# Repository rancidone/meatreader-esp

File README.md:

# Meatreader ESP32

ESP32-based wireless meat thermometer. Firmware reads up to 4 thermistor channels via ADS1115 ADC, applies Steinhart-Hart calibration, and exposes an HTTP API consumed by a web UI served from the device.

## Product Direction

This is a personal project in development, not a validated commercial thermometer. V0 demonstrated probe-to-phone readings. The later V2 board is assembled and has needed wiring repairs; the repository does not establish post-repair four-probe accuracy, Wi-Fi stability, or battery runtime. Implemented software features should not be read as hardware qualification results. The on-device display remains unfinished in MeatReader.

The [build story](https://mattmadeitwork.com/projects/meatreader/) documents the revisions and repairs.

**Web UI** (`thermometer-ui/`) is the primary interface — live dashboard, cook profiles, alerts, calibration, config, diagnostics, and firmware updates. Accessible from any browser on the local network, including mobile browsers.

**On-device TFT UI** (planned) will provide a heads-up status display with physical button navigation — no phone required during a cook.

The ESP32 firmware HTTP API is the integration surface. LAN-first; no cloud dependency.

## Repository Layout

```
firmware/          — ESP-IDF v5.5.3 C firmware (ESP32)
thermometer-ui/    — Svelte 5 + TypeScript web UI (served from device SPIFFS)
pcb/               — later board design and printable enclosure files
```

## HTTP API

All endpoints return JSON. The device runs an HTTP server on port 80.

| Method | Path | Description |
|--------|------|-------------|
| `GET` | `/dashboard` | **Consolidated** — snapshot + status + alerts in one call. `snapshot` is `null` until first sensor reading; never returns 503. Preferred for mobile clients. |
| `GET` | `/temps/latest` | Latest sensor snapshot (all channels). |
| `GET` | `/status` | Device health, uptime, firmware version, WiFi RSSI. |
| `GET` | `/device` | Static device metadata (platform, channel count, firmware). |
| `GET` | `/config` | Full config object: persisted / active / staged. |
| `PATCH` | `/config/staged` | Partial patch to staged config. |
| `POST` | `/config/apply` | Promote staged → active. |
| `POST` | `/config/commit` | Persist active → NVS. |
| `POST` | `/config/revert-staged` | Revert staged ← active. |
| `POST` | `/config/revert-active` | Revert active ← persisted (NVS). |
| `GET` | `/alerts` | Per-channel alert config + live `triggered` state. |
| `PATCH` | `/alerts/staged` | Update staged alert config. |
| `GET` | `/profiles` | All 8 cook profile slots (empty slots have `name=""`). |
| `PUT` | `/profiles/{id}` | Write a cook profile slot. |
| `DELETE` | `/profiles/{id}` | Clear a cook profile slot. |
| `GET` | `/calibration/live` | Live calibration reading for a channel (`?ch=N`). |
| `POST` | `/calibration/session/start` | Begin calibration session. |
| `POST` | `/calibration/point/capture` | Capture a calibration point. |
| `POST` | `/calibration/solve` | Solve Steinhart-Hart coefficients from captured points. |
| `POST` | `/calibration/accept` | Write solved coefficients to staged config. |
| `GET` | `/metrics` | Prometheus text metrics (temperature, resistance, ADC, RSSI, uptime). |
| `GET` | `/events` | Server-Sent Events stream — emits snapshot JSON on each sensor tick. |
| `POST` | `/ota` | Upload firmware binary for OTA update. |
| `POST` | `/ota/rollback` | Roll back to the previous OTA partition. |

TypeScript API types are in `thermometer-ui/src/lib/api/types.ts`. The browser client is in `thermometer-ui/src/lib/api/client.ts`, with the live SSE transport in `thermometer-ui/src/lib/api/live.ts`. There is no separate native mobile application in this repository.

The [archived hardware repository](https://github.com/rancidone/meatreader-pcb) preserves earlier hardware work. Check the physical board revision against `pcb/` and the constants in `firmware/components/board/` before building or flashing.

## Production Build & Flash

Flash the full self-contained firmware (ESP32 + web UI served from SPIFFS):

### Prerequisites

1. Install [ESP-IDF v5.5.3](https://docs.espressif.com/projects/esp-idf/en/v5.5.3/esp32/get-started/)
2. Install Node.js 22.12+ (or a compatible newer LTS release).

### One-command flash

```bash
source $IDF_PATH/export.sh   # activate ESP-IDF toolchain
./build-all.sh               # builds UI, then builds + flashes firmware + SPIFFS image
```

### Manual steps

```bash
# 1. Build the web UI
cd thermometer-ui && npm install && npm run build && cd ..

# 2. Build firmware (SPIFFS image is auto-generated from thermometer-ui/dist/)
cd firmware && idf.py build

# 3. Flash everything (firmware + SPIFFS image)
idf.py flash
```

### Development (no flashing needed)

```bash
cd thermometer-ui && npm ci && npm run dev
```

Before starting, set the proxy targets in `thermometer-ui/vite.config.ts` to your device's LAN address. No device is needed to inspect the interface shell, but live temperatures and calibration require connected hardware; a disconnected dashboard is not a measurement demonstration.

## Checks without hardware

```sh
cd thermometer-ui
npm ci
npm test
npm run build
```

Host-side thermistor math tests can be run separately:

```sh
cmake -S firmware/tests -B /tmp/meatreader-host-tests
cmake --build /tmp/meatreader-host-tests
ctest --test-dir /tmp/meatreader-host-tests --output-on-failure
```

These checks exercise software, not probe calibration, repaired boards, enclosure fit, or runtime. Record those results on the actual hardware before describing V2 as validated.

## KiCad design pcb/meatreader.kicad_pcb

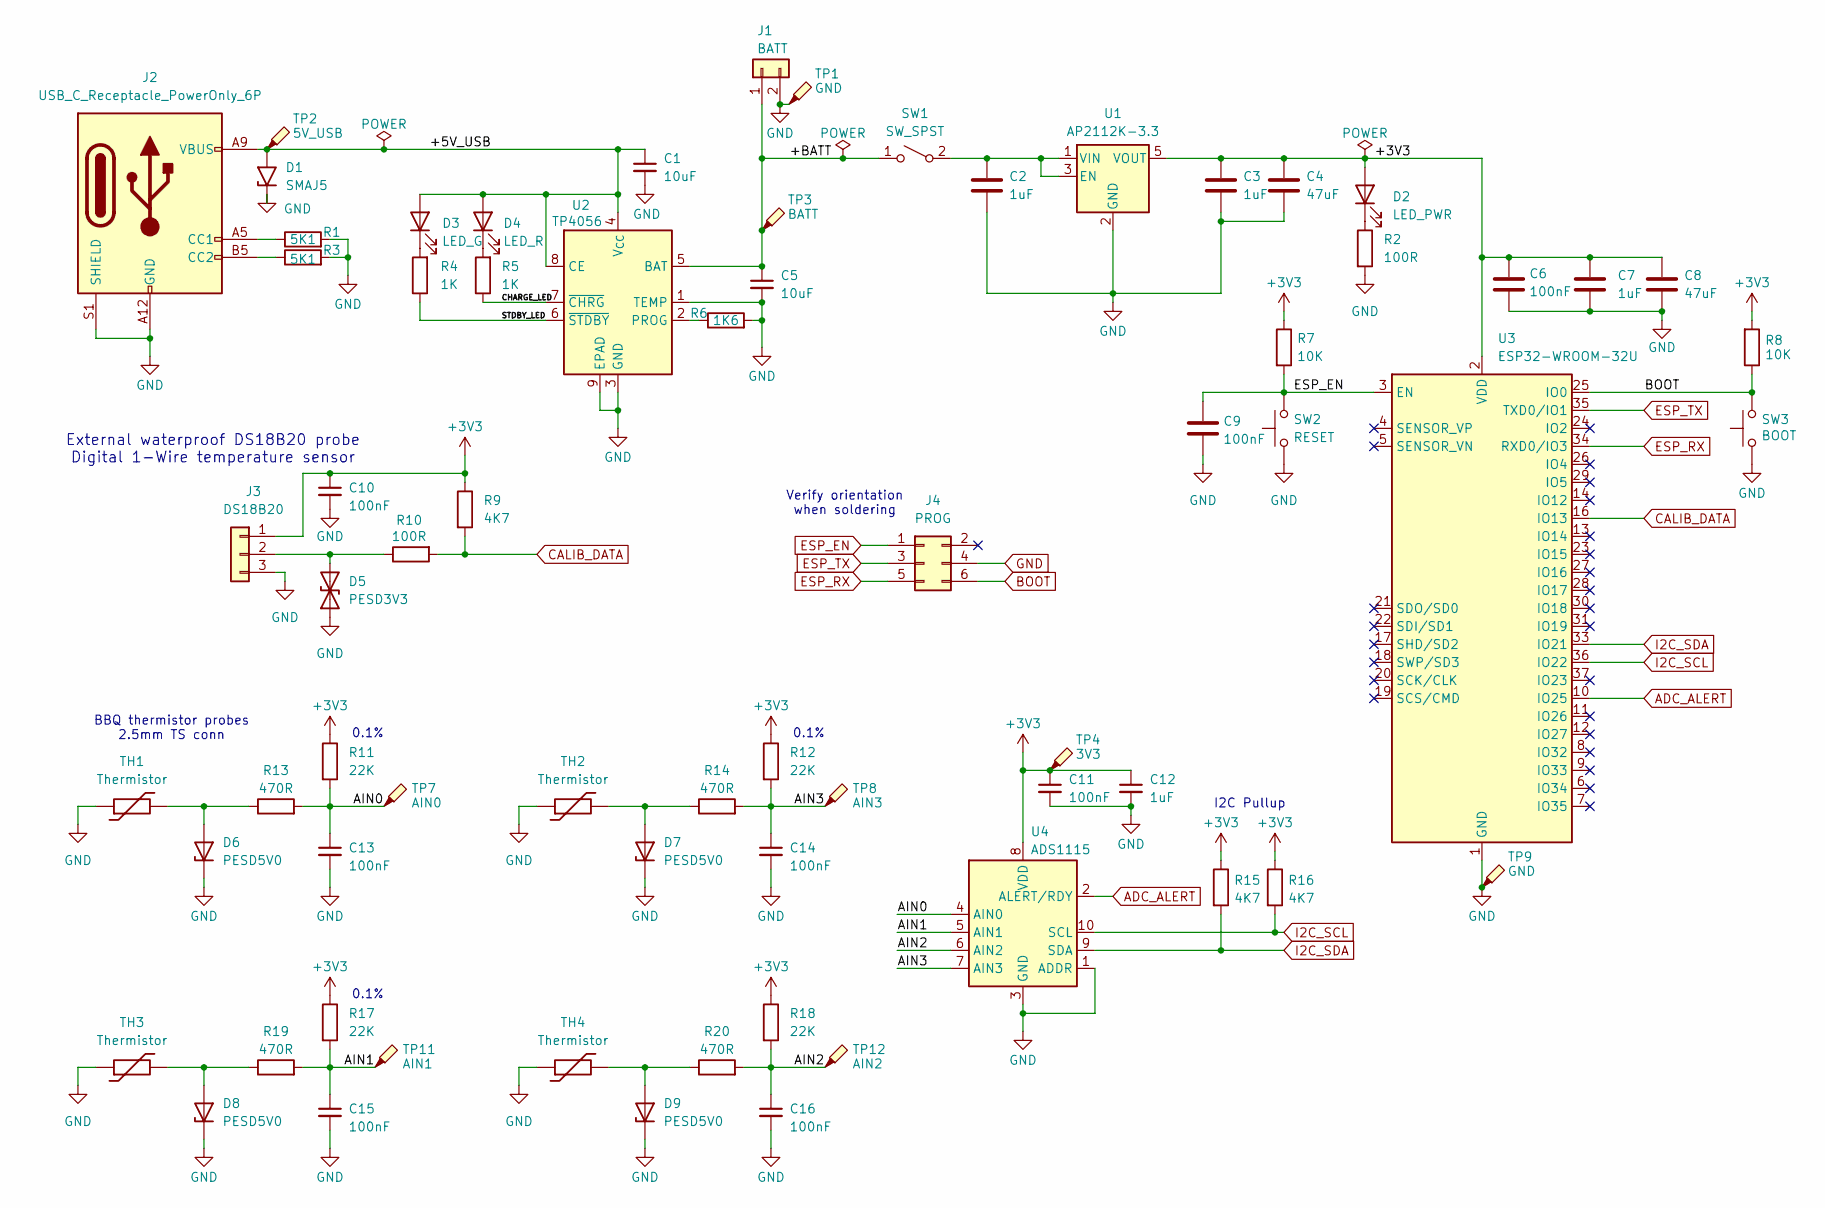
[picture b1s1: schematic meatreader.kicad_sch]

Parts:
C1, C5: 10uF; C_0805_2012Metric_Pad1.18x1.45mm_HandSolder
C2, C3, C7, C12: 1uF; C_0603_1608Metric_Pad1.08x0.95mm_HandSolder
C4: 47uF; R_0805_2012Metric_Pad1.20x1.40mm_HandSolder
C6, C9, C10, C11, C13, C14, C15, C16: 100nF; C_0603_1608Metric_Pad1.08x0.95mm_HandSolder
C8: 47uF; C_0805_2012Metric_Pad1.18x1.45mm_HandSolder
D1: SMAJ5; D_SMA_Handsoldering; LCSC C19077497
D2: LED_PWR; LED_D3.0mm
D3: LED_G; LED_D3.0mm
D4: LED_R; LED_D3.0mm
D5: PESD3V3; D_SOD-323_HandSoldering
D6, D7, D8, D9: PESD5V0; D_SOD-323_HandSoldering
J1: BATT; JST_PH_B2B-PH-K_1x02_P2.00mm_Vertical
J2: USB_C_Receptacle_PowerOnly_6P; USB_C_Receptacle_GCT_USB4125-xx-x_6P_TopMnt_Horizontal
J3: DS18B20; JST_PH_B3B-PH-K_1x03_P2.00mm_Vertical
J4: PROG; PinHeader_2x03_P1.27mm_Vertical_SMD
R1, R3: 5K1; R_0603_1608Metric_Pad0.98x0.95mm_HandSolder
R2: 100R; R_0603_1608Metric_Pad0.98x0.95mm_HandSolder
R4, R5: 1K; R_0603_1608Metric_Pad0.98x0.95mm_HandSolder; LCSC C11702
R6: 1K6; R_0603_1608Metric_Pad0.98x0.95mm_HandSolder
R7, R8: 10K; R_0603_1608Metric_Pad0.98x0.95mm_HandSolder
R9: 4K7; R_0603_1608Metric
R10: 100R; R_0603_1608Metric
R11, R12, R17, R18: 22K; R_1206_3216Metric_Pad1.30x1.75mm_HandSolder
R13, R14, R19, R20: 470R; R_0603_1608Metric_Pad0.98x0.95mm_HandSolder
R15, R16: 4K7; R_0603_1608Metric_Pad0.98x0.95mm_HandSolder
SW1: SW_SPST; JST_PH_B2B-PH-K_1x02_P2.00mm_Vertical
SW2: RESET; 6x3.5 Tactile Switch
SW3: BOOT; 6x3.5 Tactile Switch
TH1, TH2, TH3, TH4: Thermistor; PJ-209
TP1, TP9: GND; TestPoint_THTPad_D2.5mm_Drill1.2mm
TP2: 5V_USB; TestPoint_THTPad_D2.5mm_Drill1.2mm
TP3: BATT; TestPoint_THTPad_D2.5mm_Drill1.2mm
TP4: 3V3; TestPoint_THTPad_D2.5mm_Drill1.2mm
TP7: AIN0; TestPoint_Pad_D2.5mm
TP8: AIN3; TestPoint_Pad_D2.5mm
TP11: AIN1; TestPoint_Pad_D2.5mm
TP12: AIN2; TestPoint_Pad_D2.5mm
U1: AP2112K-3.3; SOT-23-5
U2: TP4056; SOIC-8-1EP_3.9x4.9mm_P1.27mm_EP2.41x3.3mm
U3: ESP32-WROOM-32U
U4: ADS1115; TSSOP-10_3x3mm_P0.5mm

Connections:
+3V3: C3.1, C4.1, C6.1, C7.1, C8.1, C10.1, C11.1, C12.1, D2.2 (A), J3.1, R7.1, R8.2, R9.1, R11.1, R12.1, R15.1, R16.1, R17.1, R18.1, TP4.1 (1_1), U1.5 (VOUT), U3.2 (VDD), U4.8 (VDD)
/+5V_USB: C1.1, D1.2 (A2), D3.2 (A), D4.2 (A), J2.A9 (VBUS), J2.B9 (VBUS), TP2.1 (1_1), U2.4 (V_{CC}), U2.8 (CE)
/+BATT: C5.1, J1.1, SW1.1 (B), TP3.1 (1_1), U2.5 (BAT)
/AIN0: C13.1, R11.2, R13.2, TP7.1 (1_1), U4.4 (AIN0)
/AIN1: C15.1, R17.2, R19.2, TP11.1 (1_1), U4.5 (AIN1)
/AIN2: C16.1, R18.2, R20.2, TP12.1 (1_1), U4.6 (AIN2)
/AIN3: C14.1, R12.2, R14.2, TP8.1 (1_1), U4.7 (AIN3)
/CHARGE_LED: R5.1, U2.7 (~CHRG)
/STDBY_LED: R4.1, U2.6 (~STDBY)
ADC_ALERT: U3.10 (IO25), U4.2 (ALERT/RDY)
BOOT: J4.6, R8.1, SW3.1, U3.25 (IO0)
CALIB_DATA: R9.2, R10.2, U3.16 (IO13)
ESP_EN: C9.1, J4.1, R7.2, SW2.2, U3.3 (EN)
ESP_RX: J4.5, U3.34 (RXD0/IO3)
ESP_TX: J4.3, U3.35 (TXD0/IO1)
GND: C1.2, C2.2, C3.2, C4.2, C5.2, C6.2, C7.2, C8.2, C9.2, C10.2, C11.2, C12.2, C13.2, C14.2, C15.2, C16.2, D1.1 (A1), D5.1 (A1), D6.1 (K), D7.1 (K), D8.1 (K), D9.1 (K), J1.2, J2.A12 (GND), J2.B12 (GND), J2.S1 (SHIELD), J2.SH, J3.3, J4.4, R1.2, R2.2, R3.2, R6.2, SW2.1, SW3.2, TH1.1, TH2.1, TH3.1, TH4.1, TP1.1 (1_1), TP9.1 (1_1), U1.2 (GND), U2.1 (TEMP), U2.3 (GND), U2.9 (EPAD), U3.1 (GND), U3.15 (GND), U3.38 (GND), U3.39 (GND), U4.1 (ADDR), U4.3 (GND)
I2C_SCL: R16.2, U3.36 (IO22), U4.10 (SCL)
I2C_SDA: R15.2, U3.33 (IO21), U4.9 (SDA)
unnamed: D2.1 (K), R2.1
unnamed: D3.1 (K), R4.2
unnamed: D4.1 (K), R5.2
unnamed: D5.2 (A2), J3.2, R10.1
unnamed: D6.2 (A), R13.1, TH1.2
unnamed: D7.2 (A), R14.1, TH2.2
unnamed: D8.2 (A), R19.1, TH3.2
unnamed: D9.2 (A), R20.1, TH4.2
unnamed: J2.A5 (CC1), R1.1
unnamed: J2.B5 (CC2), R3.1
unnamed: C2.1, SW1.2 (A), U1.1 (VIN), U1.3 (EN)
unnamed: R6.1, U2.2 (PROG)

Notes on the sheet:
0.1%
Verify orientation when soldering
BBQ thermistor probes 2.5mm TS conn
External waterproof DS18B20 probe Digital 1-Wire temperature sensor
I2C Pullup

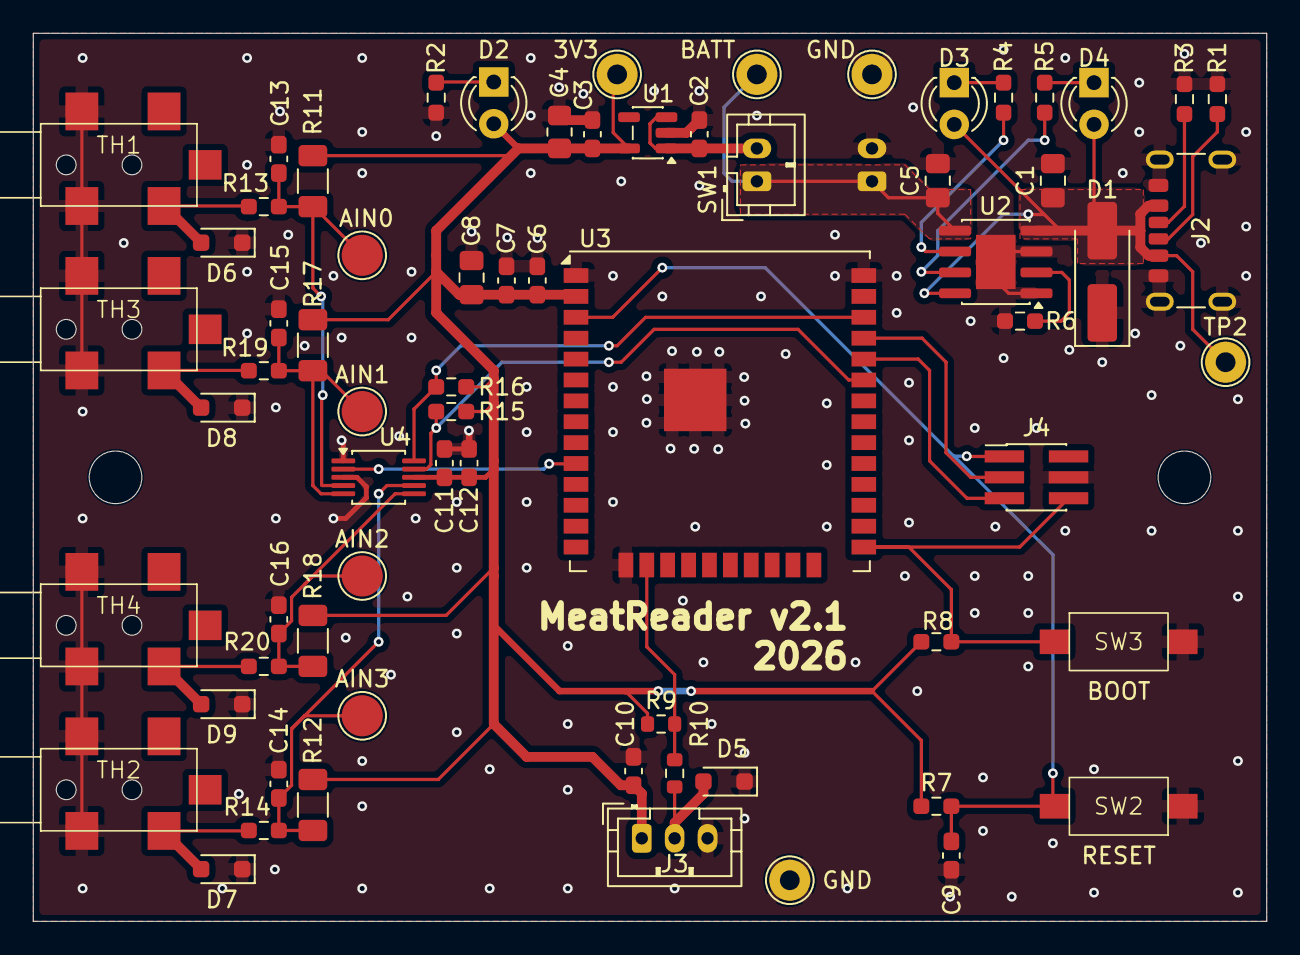
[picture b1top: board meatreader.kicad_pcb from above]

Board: 2 copper layers, 75.0 x 54.0 mm, 69 parts (1 on the bottom side), 30 nets.

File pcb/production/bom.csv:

Designator,Footprint,Quantity,Value,LCSC Part #
"C1, C5",0805,2,10uF,
"C10, C11, C6, C9",0603,4,100nF,
"C12, C2, C3, C7",0603,4,1uF,
"C13, C14, C15, C16",0603,4,47nF,
"C4, C8",0805,2,47uF,
D1,D_SMA_Handsoldering,1,SMAJ5,C19077497
D2,LED_D3.0mm,1,LED_PWR,
D3,LED_D3.0mm,1,LED_G,
D4,LED_D3.0mm,1,LED_R,
D5,D_SOD-323_HandSoldering,1,PESD3V3,
"D6, D7, D8, D9",D_SOD-323_HandSoldering,4,PESD5V0,
J1,JST_PH_B2B-PH-K_1x02_P2.00mm_Vertical,1,BATT,
J2,USB_C_Receptacle_GCT_USB4125-xx-x_6P_TopMnt_Horizontal,1,USB_C_Receptacle_PowerOnly_6P,
J3,JST_PH_B3B-PH-K_1x03_P2.00mm_Vertical,1,DS18B20,
J4,PinHeader_2x03_P1.27mm_Vertical_SMD,1,PROG,
"R1, R3",0603,2,5K1,
"R10, R2",0603,2,100R,
"R11, R12, R17, R18",1206,4,22K,
"R13, R14, R19, R20",0603,4,470R,
"R15, R16, R9",0603,3,4K7,
"R4, R5",0603,2,1K,C11702
R6,0603,1,1K6,
"R7, R8",0603,2,10K,
SW1,JST_PH_B2B-PH-K_1x02_P2.00mm_Vertical,1,SW_SPST,
SW2,6x3.5 Tactile Switch,1,RESET,
SW3,6x3.5 Tactile Switch,1,BOOT,
"TH1, TH2, TH3, TH4",PJ-209,4,Thermistor,
"TP1, TP9",TestPoint_THTPad_D2.5mm_Drill1.2mm,2,GND,
TP11,TestPoint_Pad_D2.5mm,1,AIN1,
TP12,TestPoint_Pad_D2.5mm,1,AIN2,
TP2,TestPoint_THTPad_D2.5mm_Drill1.2mm,1,5V_USB,
TP3,TestPoint_THTPad_D2.5mm_Drill1.2mm,1,BATT,
TP4,TestPoint_THTPad_D2.5mm_Drill1.2mm,1,3V3,
TP7,TestPoint_Pad_D2.5mm,1,AIN0,
TP8,TestPoint_Pad_D2.5mm,1,AIN3,
U1,SOT-23-5,1,AP2112K-3.3,
U2,SOIC-8-1EP_3.9x4.9mm_P1.27mm_EP2.41x3.3mm,1,TP4056,
U3,ESP32-WROOM-32U,1,ESP32-WROOM-32U,
U4,TSSOP-10_3x3mm_P0.5mm,1,ADS1115,

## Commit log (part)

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2026-03-08 Mark Phase 2 complete in TODO.md
2026-03-08 Shrink TODO.md
2026-03-08 chore: mark done: remove raw fields from ChannelCard, add to Diagnostics
2026-03-08 chore: mark done: channel labels (firmware + UI)
2026-03-08 chore: mark done: cook timer + predicted done time (Phase 2 complete)
2026-03-08 chore: mark done: Phase 3 SSE endpoint + UI live updates
2026-03-08 chore: compact TODO.md — remove completed phases 1-3
2026-03-08 Add agentkit config
2026-03-08 chore(agentkit): add meatreader-specific extraction adapter
2026-03-08 chore: remove python cache artifact from adapter
2026-03-08 chore(gitignore): harden python cache ignore rules
2026-03-08 Fix events route snapshot_to_json call signature
2026-03-08 Harden startup script defaults for public-repo safety
2026-03-08 Remove direnv integration from startup script
2026-03-08 sensor_mgr: throttle repeated channel fault warnings
2026-03-08 Harden SSE stream handling and smooth noisy probe reads
2026-03-08 Harden startup script for minimal container environments
2026-03-08 startup: prefer python3.13 for esp-idf setup
2026-03-08 chore: mark firmware cook profile TODO items complete
2026-03-08 chore: mark UI cook profile TODO items complete
2026-03-08 chore: mark Phase 4 stall detection TODO items complete
2026-03-08 Fix chart default ranges and add sparkline bounds labels
2026-03-08 Tighten agentkit governance thresholds and strict mode
2026-03-11 Update TODOs and add main component manifest
2026-03-11 Update gitignore
2026-03-13 docs(readme): document native mobile app as primary product direction
    Native mobile app (React Native + Expo) is now the primary UX surface.
    Web UI is repositioned as local admin/setup console. PWA is no longer
    the recommended distribution path. TFT UI track noted as in-progress.
2026-03-13 chore: scaffold mobile-app/ directory and document monorepo layout
    Adds mobile-app/ as the reserved location for the React Native + Expo
    native app (Phase 9 will initialize it). Documents the three-package
    repo layout in README.md.
2026-03-13 chore: extract shared API types to @meatreader/api-types workspace package
    Creates packages/meatreader-api-types/ as the canonical home for
    firmware-derived TypeScript interfaces. thermometer-ui re-exports from
    it. Root package.json establishes npm workspaces for all three packages.
    mobile-app will add the same dependency during Phase 9 initialization.
2026-03-13 docs(readme): capture v1 mobile feature scope
    Documents the minimum feature set for the first native app release:
    live dashboard, device connection by IP, cook profiles, alert visibility,
    and device health. Out-of-scope items (calibration, config, OTA) remain
    in the web admin console.
2026-03-13 feat(mobile-app): initialize Expo + TypeScript app with workspace structure
    Scaffolds mobile-app/ using create-expo-app (blank-typescript template,
    Expo 55). Wires in @meatreader/api-types via npm workspace. Creates
    src/api/client.ts (HTTP client over firmware API), src/store/device.ts
    (saved device registry stub), and src/screens/ + src/navigation/
    directory stubs for Phase 9. Typecheck passes clean.
2026-03-13 feat(mobile-app): implement polling hook, AsyncStorage device registry, and arch wiring
    - src/store/device.ts: AsyncStorage-backed saved device registry with
    add/remove/touch/active-IP helpers
    - src/api/usePolling.ts: interval polling hook that retains stale data
    on error and cancels cleanly on unmount
    - App.tsx: proof-of-concept entry wiring client + polling + device store;
    replaced by navigation shell in Phase 9
2026-03-13 feat(mobile-app): add expo-router navigation shell with tab layout
    - Switches entry point to expo-router/entry (file-based routing)
    - app/_layout.tsx: root Stack with no header
    - app/index.tsx: redirects to /(tabs)/dashboard
    - app/(tabs)/_layout.tsx: tab bar with Dashboard / Devices / Profiles tabs
    - app/(tabs)/dashboard|devices|profiles.tsx: placeholder screens
    - Adds expo-router ~55.0.5, expo-linking, expo-constants,
2026-03-13 feat(mobile-app): implement instrument-panel dashboard UX
    - Large 40pt temperature tiles per enabled channel (2-column grid)
    - Alert and stall badges on individual tiles; alert border highlight
    - Quality indicator dot (ok=green, stale=orange, disabled=gray, error=red)
    - Connection banner shows live/disconnected/connecting state with device IP
    - Polls /temps/latest every 2s via usePolling; retains stale data on error
    - Graceful empty state when no device is configured
2026-03-13 feat(mobile-app): implement device onboarding and management screen
    - IP/hostname text input with basic validation; auto-activates first device added
    - Saved device list: tap to activate (green border + dot), Remove button with confirm
    - Clears or reassigns active device when the active one is removed
    - KeyboardAvoidingView for iOS; FlatList for arbitrary device count
    - Empty state with onboarding hint
2026-03-13 feat(mobile-app): implement cook profiles and alerts screens
    - packages/meatreader-api-types: add AlertStatus / AlertsResponse types
    - src/api/client.ts: add getAlerts(), patchAlerts(), postConfigApply()
    - app/(tabs)/profiles.tsx: list non-empty profiles; Apply button patches
    PATCH /alerts/staged with stage targets then POST /config/apply
    - app/(tabs)/alerts.tsx: polls /temps/latest + /alerts every 3s; shows
    triggered alert rows with target temp, stall-detected section, and
2026-03-13 fix(thermometer-ui): resolve PWA production build failure
    vite-plugin-pwa's injectManifest strategy calls workbox-build to inject
    self.__WB_MANIFEST into the compiled SW. Our custom SW does not use
    precaching, so the token never survived Rollup's tree-shaking, causing
    the 'no injection point found' error.
    Fix: set injectionPoint: undefined in the injectManifest config block,
    which causes vite-plugin-pwa to skip the workbox manifest injection step
2026-03-13 refactor(thermometer-ui): remove PWA install prompt and Web Push subscription UI
    Native mobile app is now the primary UX. Remove product work that no
    longer matches the roadmap:
    - App.svelte: drop beforeinstallprompt handler, install banner, and
    install-banner CSS — PWA install is not the distribution path
    - Config.svelte: drop Web Push subscribe/unsubscribe UI, pushSubscribed
    state, pushPending state, and push subscription check effect
2026-03-13 fix(thermometer-ui): narrow-screen responsiveness for mobile browser use
    - App.svelte: at ≤600px, topbar stacks wordmark above a scrollable tab
    row (overflow-x: auto, no scrollbar chrome); tab font/padding reduced;
    content padding tightened to 0.75rem sides
    - Dashboard.svelte: channel grid uses minmax(min(280px, 100%), 1fr) so
    cards don't overflow on 320px screens (single column auto-collapses)
    - tab buttons: white-space: nowrap prevents mid-label line breaks
2026-03-13 chore: mark Phase 8, 9, 10 complete in TODO
2026-03-13 fix: resolve main task stack overflow on boot
    device_config_t (~2 KB) was stack-allocated in app_main, exhausting the
    4096-byte main task stack during the boot sequence. Two fixes:
    - Raise CONFIG_ESP_MAIN_TASK_STACK_SIZE to 8192 in sdkconfig.defaults
    - Heap-allocate device_config_t in app_main (freed after WiFi init)
2026-03-13 chore: mark boot stack overflow bug resolved in TODO
2026-06-19 fix: resolve ESP-IDF v6 component dependency build errors
    Add esp_driver_i2c to ads1115 and i2c_manager REQUIRES; replace unknown
    'json' component with espressif__cjson in alert_mgr (PRIV_REQUIRES) and
    http_server (REQUIRES). Add espressif/cjson managed dependency and fix
    rollup native module install for UI dist build.
2026-06-19 feat: hardware mapping fixes, simplified config, all-channel calibration
    - Fix open-circuit detection thresholds (raw 32000→22000, ohms 2M→500k)
    so floating AIN inputs at ~3.2V are correctly detected as open
    - Map probe channels to AIN1/AIN2 (AIN0/AIN3 unused on this board rev)
    - Add temperature_f to /temps/latest JSON response
    - Show °C/°F in sensor_mgr tick logs
    - Remove staged config layer — PATCH /config edits active directly;
2026-06-21 fix: embed git hash in build version, fix UI rebuild pipeline, fix Console reactive loop
    - CMakeLists.txt: append short git hash to PROJECT_VER (e.g. 0.5.0-abc1234)
    so OTA updates are uniquely identifiable via GET /device firmware_version
    - http_server CMakeLists: switch to add_custom_target(ALL) so Svelte UI is
    built unconditionally on every idf.py build; fixes silent skip when dist/
    files were newer than tracked sources
    - Firmware.svelte: convert $derived.by to plain function to fix production
2026-06-21 fix: break consoleLog.push() reactive loop via untrack
    push() reads this.entries (reactive $state) to spread it, which caused every
    $effect calling push() to track consoleLog.entries as a dependency. Writing
    entries inside the same call then re-triggered the effect infinitely.
    untrack() when reading entries breaks the cycle.
2026-06-21 fix: console logs events only, not every snapshot
    Removed per-snapshot logging that caused a 500-item list re-render every
    second. Console now logs only SSE errors/reconnects and device connectivity
    changes. All push() calls wrapped in untrack() to prevent reactive loops.
2026-06-21 fix: I2C bus recovery + sensor task stack increase to prevent freeze
    When the ADS1115 gets into a bad state (SDA held low after a glitch),
    all channels error continuously. After 3 such cycles the sensor task now
    calls i2c_master_bus_reset() to flush the stuck slave before the task
    watchdog would fire and reset the whole chip.
    Also increases sensor_mgr task stack from 4096 → 6144 bytes to give the
    I2C driver and floating-point math adequate headroom.
2026-06-21 fix: chart modal height so uPlot fills the container
    modal had only max-height, so flex:1 on chart-container had nothing to
    expand into — uPlot read clientHeight=0 and the chart had no visible area.
    Replaced with height: min(600px, 90vh) so flex layout works correctly.
2026-06-21 feat: cook profile stage alerts, UI blink, firmware history ring buffer
    Alert watcher (UI):
    - alertWatcher.svelte.ts tracks alert_triggered transitions per channel
    - When a stage target is hit: fires browser Notification, advances to next
    stage (patches config with next target_temp_c), or marks cook complete
    and disables the alert on final stage
    - ChannelCard pulses amber border while alert is active; click to dismiss
2026-06-21 feat: quick target input, chart expand fix, sparkline resize, build timestamp
    - Fix expand: sparkline onclick uses explicit arrow fn instead of {onclick} shorthand
    - Fix sparkline resize: ResizeObserver redraws canvas when CSS height changes (56→96px at 640px+)
    - Fix profileStore .staged.alerts → .alerts (config API returns DeviceConfig directly)
    - Add quick target number input on channel card — bypasses profile, patches alert directly
    - Remove chart series fills that were anchoring to y=0 and creating heavy overlap
    - Add History label to dashboard time-window dropdown
2026-06-21 fix: hide quick target input when a profile is selected
2026-06-21 fix: use configStore.patch so alert target updates reflect in UI
2026-06-21 feat: seed history from firmware ring buffer on dashboard mount
2026-06-21 fix: show Connected if SSE snapshot received in last 10s, not just status poll
2026-06-21 fix: move isConnected to script block as $derived (const_tag_invalid_placement)
2026-06-21 fix: light axis labels and grid lines in chart modal for dark background
2026-06-21 feat: 15s history samples, 1440 points (6h at 15s resolution)
